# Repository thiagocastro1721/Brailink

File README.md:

# Brailink
Este repositório reúne os códigos-fonte utilizados no desenvolvimento do teclado Brailink, incluindo tanto a primeira versão funcional quanto a versão final do projeto.

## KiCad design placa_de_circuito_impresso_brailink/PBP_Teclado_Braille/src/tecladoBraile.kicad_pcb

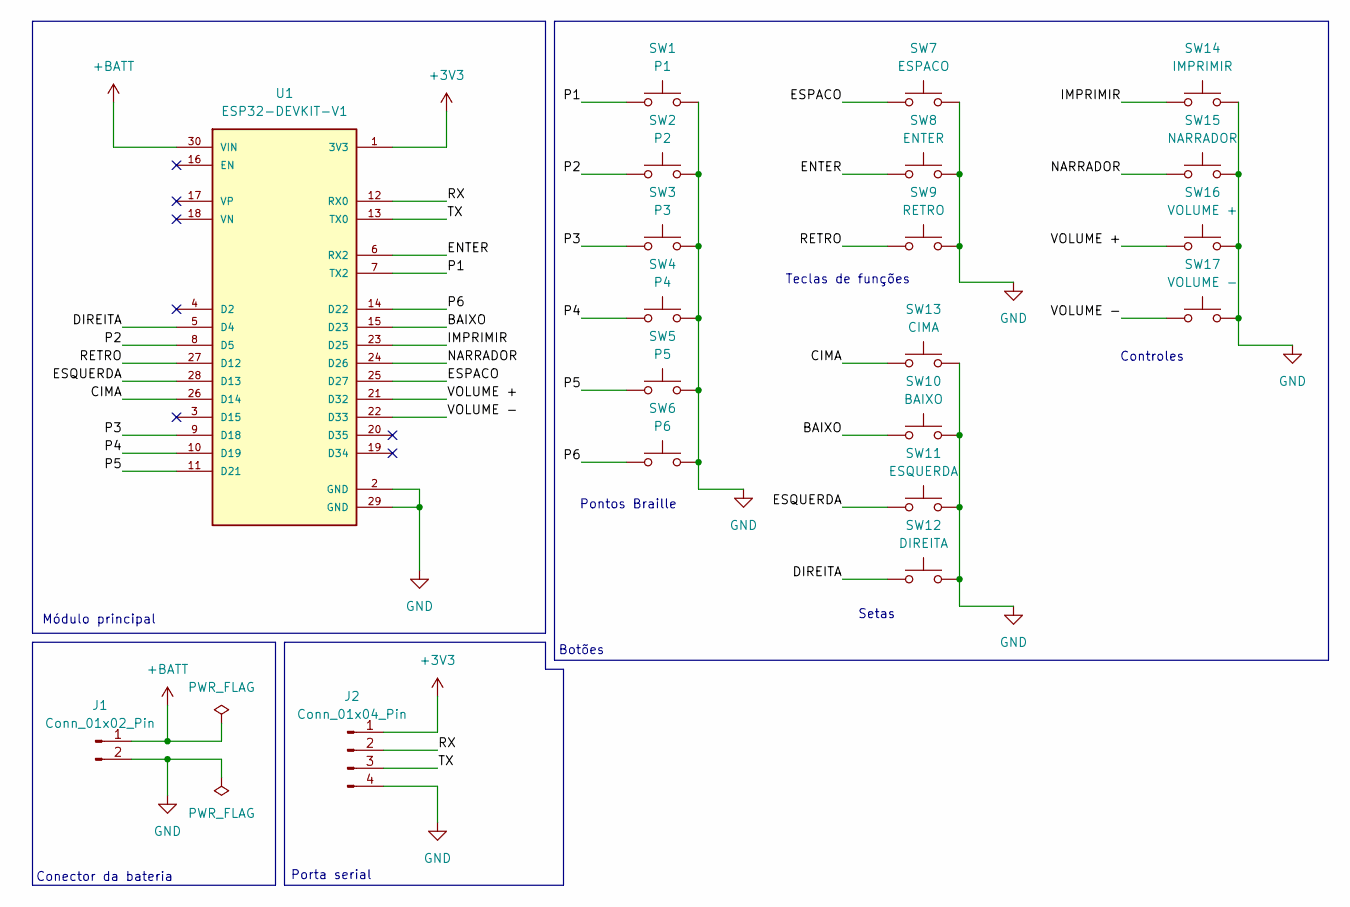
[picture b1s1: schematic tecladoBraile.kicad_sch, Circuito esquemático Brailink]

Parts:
J1: Conn_01x02_Pin; Molex_KK-254_AE-6410-02A_1x02_P2.54mm_Vertical
J2: Conn_01x04_Pin; PinHeader_1x04_P2.54mm_Vertical
SW1: P1; SW_Cherry_MX_PCB_1.00u
SW2: P2; SW_Cherry_MX_PCB_1.00u
SW3: P3; SW_Cherry_MX_PCB_1.00u
SW4: P4; SW_Cherry_MX_PCB_1.00u
SW5: P5; SW_Cherry_MX_PCB_1.00u
SW6: P6; SW_Cherry_MX_PCB_1.00u
SW7: ESPACO; SW_Cherry_MX_PCB_2.00u
SW8: ENTER; SW_Cherry_MX_PCB_1.75u
SW9: RETRO; SW_Cherry_MX_PCB_1.75u
SW10: BAIXO; SW_Cherry_MX_PCB_1.00u
SW11: ESQUERDA; SW_Cherry_MX_PCB_1.00u
SW12: DIREITA; SW_Cherry_MX_PCB_1.00u
SW13: CIMA; SW_Cherry_MX_PCB_1.00u
SW14: IMPRIMIR; SW_Cherry_MX_PCB_1.00u
SW15: NARRADOR; SW_Cherry_MX_PCB_1.00u
SW16: VOLUME +; SW_Cherry_MX_PCB_1.00u
SW17: VOLUME -; SW_Cherry_MX_PCB_1.00u
U1: ESP32-DEVKIT-V1; MODULE_ESP32_DEVKIT_V1; PARTREV N/A

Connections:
+3V3: J2.1, U1.1 (3V3)
+BATT: J1.1, U1.30 (VIN)
/BAIXO: SW10.1, U1.15 (D23)
/CIMA: SW13.1, U1.26 (D14)
/DIREITA: SW12.1, U1.5 (D4)
/ENTER: SW8.1, U1.6 (RX2)
/ESPACO: SW7.1, U1.25 (D27)
/ESQUERDA: SW11.1, U1.28 (D13)
/IMPRIMIR: SW14.1, U1.23 (D25)
/NARRADOR: SW15.1, U1.24 (D26)
/P1: SW1.1, U1.7 (TX2)
/P2: SW2.1, U1.8 (D5)
/P3: SW3.1, U1.9 (D18)
/P4: SW4.1, U1.10 (D19)
/P5: SW5.1, U1.11 (D21)
/P6: SW6.1, U1.14 (D22)
/RETRO: SW9.1, U1.27 (D12)
/RX: J2.2, U1.12 (RX0)
/TX: J2.3, U1.13 (TX0)
/VOLUME +: SW16.1, U1.21 (D32)
/VOLUME -: SW17.1, U1.22 (D33)
GND: J1.2, J2.4, SW1.2, SW2.2, SW3.2, SW4.2, SW5.2, SW6.2, SW7.2, SW8.2, SW9.2, SW10.2, SW11.2, SW12.2, SW13.2, SW14.2, SW15.2, SW16.2, SW17.2, U1.2 (GND), U1.29 (GND)

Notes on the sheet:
Botões
Pontos Braille
Setas
Teclas de funções
Controles
Porta serial
Conector da bateria
Módulo principal

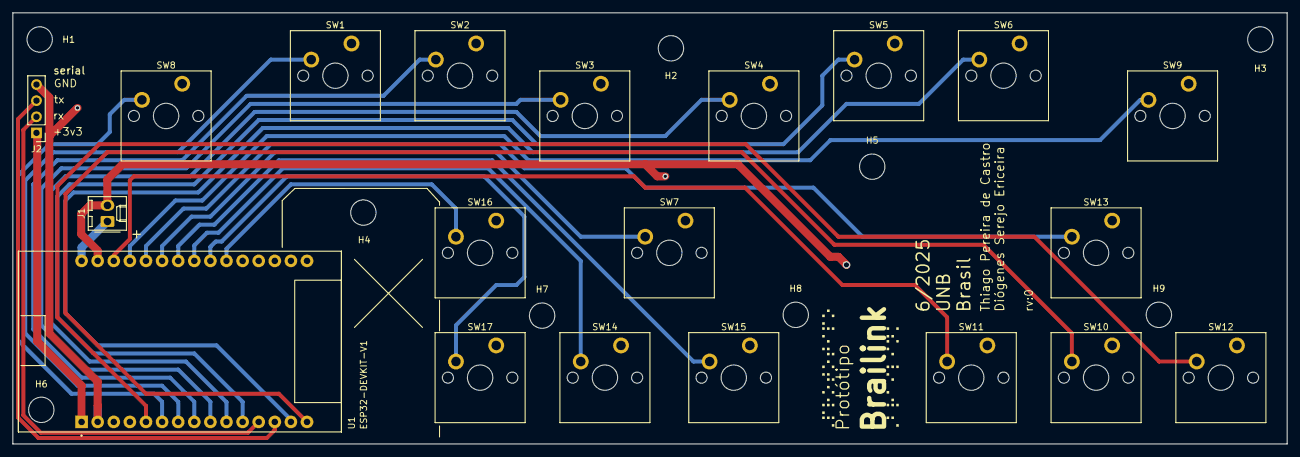
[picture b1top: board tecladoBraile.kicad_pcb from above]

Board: 2 copper layers, 201.0 x 68.0 mm, 29 parts (0 on the bottom side), 22 nets.

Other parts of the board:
H1, H2, H3, H4, H5, H6, H7, H8, H9: MountingHole_3.2mm_M3

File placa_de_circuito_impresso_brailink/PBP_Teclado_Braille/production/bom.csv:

Designator,Footprint,Quantity,Value,LCSC Part #
J1,Molex_KK-254_AE-6410-02A_1x02_P2.54mm_Vertical,1,Conn_01x02_Pin,
J2,PinHeader_1x04_P2.54mm_Vertical,1,Conn_01x04_Pin,
SW1,SW_Cherry_MX_PCB_1.00u,1,P1,
SW10,SW_Cherry_MX_PCB_1.00u,1,BAIXO,
SW11,SW_Cherry_MX_PCB_1.00u,1,ESQUERDA,
SW12,SW_Cherry_MX_PCB_1.00u,1,DIREITA,
SW13,SW_Cherry_MX_PCB_1.00u,1,CIMA,
SW14,SW_Cherry_MX_PCB_1.00u,1,IMPRIMIR,
SW15,SW_Cherry_MX_PCB_1.00u,1,NARRADOR,
SW16,SW_Cherry_MX_PCB_1.00u,1,VOLUME +,
SW17,SW_Cherry_MX_PCB_1.00u,1,VOLUME -,
SW2,SW_Cherry_MX_PCB_1.00u,1,P2,
SW3,SW_Cherry_MX_PCB_1.00u,1,P3,
SW4,SW_Cherry_MX_PCB_1.00u,1,P4,
SW5,SW_Cherry_MX_PCB_1.00u,1,P5,
SW6,SW_Cherry_MX_PCB_1.00u,1,P6,
SW7,SW_Cherry_MX_PCB_2.00u,1,ESPACO,
SW8,SW_Cherry_MX_PCB_1.75u,1,ENTER,
SW9,SW_Cherry_MX_PCB_1.75u,1,RETRO,
U1,MODULE_ESP32_DEVKIT_V1,1,ESP32-DEVKIT-V1,

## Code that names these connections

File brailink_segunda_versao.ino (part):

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// Novos pinos dos botões de controle
const int btnVolumeUp = 32;
const int btnVolumeDown = 33;
const int btnReading = 26;    // Narrador
const int btnPrint = 25;
const int btnDirUp = 14;      // Novo: Direcional cima
const int btnDirDown = 23;    // Novo: Direcional baixo  
const int btnDirLeft = 13;    // Novo: Direcional esquerda
const int btnDirRight = 4;    // Novo: Direcional direita

// Variáveis para deep sleep e controle de botão longo
unsigned long volumeDownPressTime = 0;
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
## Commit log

2025-07-27 Update brailink_segunda_versao.ino
    Remoção da biblioteca DFplayer mini.
    Mapeamento dos novos botões direcionais.
    Integração com o Narrador do Windows.
    Aumento do tempo de Inatividade de 2 minutos para 1 hora.
2025-08-17 Delete brailink_terceira_versao_botoes_extras.ino
    Código incompleto.
2025-08-17 Furos rebaixados e proteção do teclado concluída.
    Os furos de carregamento da bateria e de switch liga e desliga foram rebaixados para que o cabo possa se conectar perfeitamente para carregamento. Foi feita a estrutura de proteção do teclado para qu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
2025-08-17 Furos rebaixados e proteção do teclado finalizada.
    Os furos de carregamento e de switch liga e desliga foram rebaixados para que o cabo usb de carregamento pudesse se conectar perfeitamente à placa de carregamento da bateria. A proteção do teclado fo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
2025-08-17 Furos rebaixados e proteção finalizada.
    Os furos de carregamento e de switch (liga e desliga) foram rebaixados para que o cabo de carregamento USB passa se conectar perfeitamente à placa da bateria.
    A proteção do teclado foi projetada para proteger o usuário de eventuais toques nas peças eletrônicas.
2025-08-17 Delete arquivo_stl_case_v2.2_para_impressao_3d.zip
    Há uma pasta com o mesmo propósito.
2025-08-17 Delete arquivo_stl_case_v2_para_impressao_3d directory
    Há uma versão mais atualizada corrigindo erros desta versão.
